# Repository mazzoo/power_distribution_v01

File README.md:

power_distribution_v01

power distribution board using XT60 connectors
and fuses with LED indicator for blown fuses

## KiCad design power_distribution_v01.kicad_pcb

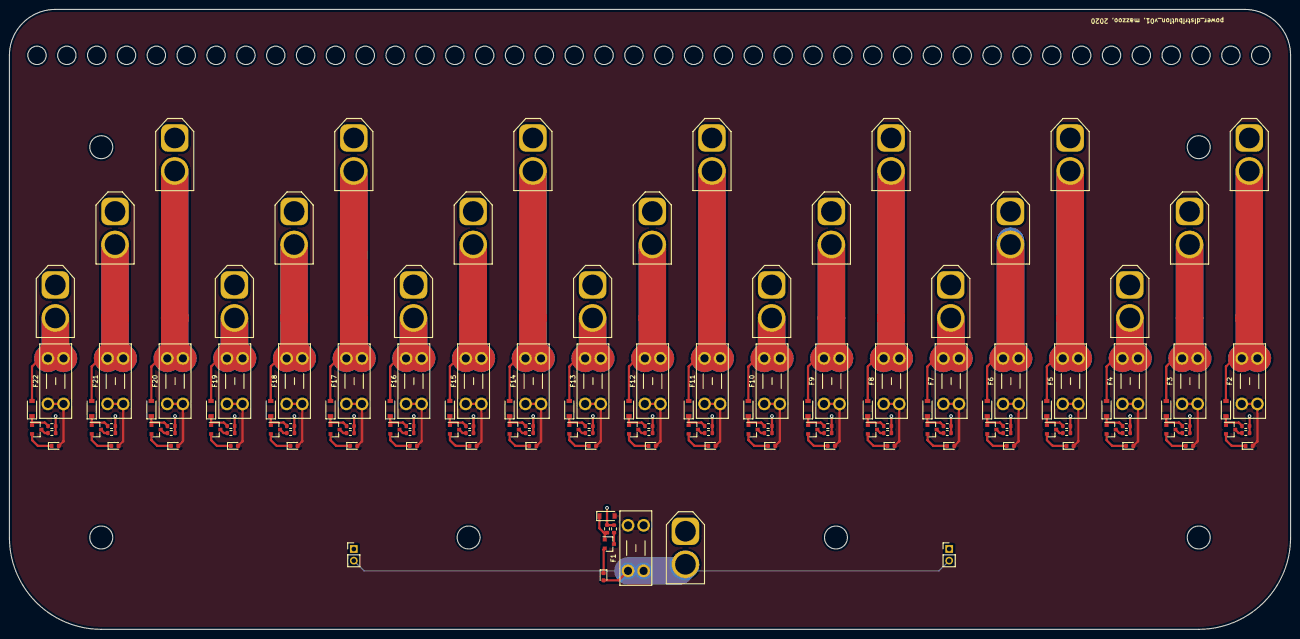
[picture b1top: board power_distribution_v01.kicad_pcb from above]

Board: 2 copper layers, 279.0 x 135.0 mm, 156 parts (0 on the bottom side), 90 nets.

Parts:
D1, D3, D5, D7, D9, D11, D13, D15, D17, D19, D21, D23, D25, D27, D29, D31, D33, D35, D37, D39, D41, D43: KT-0603R; LED_0603_1608Metric
D2, D4, D6, D8, D10, D12, D14, D16, D18, D20, D22, D24, D26, D28, D30, D32, D34, D36, D38, D40, D42, D44: 1N4148W; D_SOD-123
F1, F2, F3, F4, F5, F6, F7, F8, F9, F10, F11, F12, F13, F14, F15, F16, F17, F18, F19, F20, F21, F22: Fuse_Small; Fuseholder_Blade_Mini_Keystone_3568
J1: Conn_01x02_Male; AMASS_XT60-M_1x02_P7.20mm_Vertical
J2, J3, J4, J5, J6, J7, J8, J9, J10, J11, J12, J13, J14, J15, J16, J17, J18, J19, J20, J21, J22: Conn_01x02_Female; AMASS_XT60-F_1x02_P7.20mm_Vertical
J101, J102: Conn_01x02_Male; PinHeader_1x02_P2.54mm_Vertical
Q1, Q2, Q3, Q4, Q5, Q6, Q7, Q8, Q9, Q10, Q11, Q12, Q13, Q14, Q15, Q16, Q17, Q18, Q19, Q20, Q21, Q22: S9012; SOT-23
R1, R3, R5, R7, R9, R11, R13, R15, R17, R19, R21, R23, R25, R27, R29, R31, R33, R35, R37, R39, R41, R43: 1k; R_0603_1608Metric
R2, R4, R6, R8, R10, R12, R14, R16, R18, R20, R22, R24, R26, R28, R30, R32, R34, R36, R38, R40, R42, R44: 47k; R_0603_1608Metric

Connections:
+12V: D2.2, D3.2, D5.2, D7.2, D9.2, D11.2, D13.2, D15.2, D17.2, D19.2, D21.2, D23.2, D25.2, D27.2, D29.2, D31.2, D33.2, D35.2, D37.2, D39.2, D41.2, D43.2, F1.2, F2.1, F3.1, F4.1, F5.1, F6.1, F7.1, F8.1, F9.1, F10.1, F11.1, F12.1, F13.1, F14.1, F15.1, F16.1, F17.1, F18.1, F19.1, F20.1, F21.1, F22.1
GND: J1.1, J2.1, J3.1, J4.1, J5.1, J6.1, J7.1, J8.1, J9.1, J10.1, J11.1, J12.1, J13.1, J14.1, J15.1, J16.1, J17.1, J18.1, J19.1, J20.1, J21.1, J22.1, J101.1, J102.1, R1.2, R2.2, R3.2, R4.2, R5.2, R6.2, R7.2, R8.2, R9.2, R10.2, R11.2, R12.2, R13.2, R14.2, R15.2, R16.2, R17.2, R18.2, R19.2, R20.2, R21.2, R22.2, R23.2, R24.2, R25.2, R26.2, R27.2, R28.2, R29.2, R30.2, R31.2, R32.2, R33.2, R34.2, R35.2, R36.2, R37.2, R38.2, R39.2, R40.2, R41.2, R42.2, R43.2, R44.2
unnamed: D1.1, Q1.2
unnamed: D2.1, Q1.1, R2.1
unnamed: D3.1, Q2.2
unnamed: D4.1, Q2.1, R4.1
unnamed: D4.2, F2.2, J2.2
unnamed: D5.1, Q3.2
unnamed: D6.1, Q3.1, R6.1
unnamed: D6.2, F3.2, J3.2
unnamed: D7.1, Q4.2
unnamed: D8.1, Q4.1, R8.1
unnamed: D8.2, F4.2, J4.2
unnamed: D9.1, Q5.2
unnamed: D10.1, Q5.1, R10.1
unnamed: D10.2, F5.2, J5.2
unnamed: D11.1, Q6.2
unnamed: D12.1, Q6.1, R12.1
unnamed: D12.2, F6.2, J6.2
unnamed: D13.1, Q7.2
unnamed: D14.1, Q7.1, R14.1
unnamed: D14.2, F7.2, J7.2
unnamed: D15.1, Q8.2
unnamed: D16.1, Q8.1, R16.1
unnamed: D16.2, F8.2, J8.2
unnamed: D17.1, Q9.2
unnamed: D18.1, Q9.1, R18.1
unnamed: D18.2, F9.2, J9.2
unnamed: D19.1, Q10.2
unnamed: D20.1, Q10.1, R20.1
unnamed: D20.2, F10.2, J10.2
unnamed: D21.1, Q11.2
unnamed: D22.1, Q11.1, R22.1
unnamed: D22.2, F11.2, J11.2
unnamed: D23.1, Q12.2
unnamed: D24.1, Q12.1, R24.1
unnamed: D24.2, F12.2, J12.2
unnamed: D25.1, Q13.2
unnamed: D26.1, Q13.1, R26.1
unnamed: D26.2, F13.2, J13.2
unnamed: D27.1, Q14.2
unnamed: D28.1, Q14.1, R28.1
unnamed: D28.2, F14.2, J14.2
unnamed: D29.1, Q15.2
unnamed: D30.1, Q15.1, R30.1
unnamed: D30.2, F15.2, J15.2
unnamed: D31.1, Q16.2
unnamed: D32.1, Q16.1, R32.1
unnamed: D32.2, F16.2, J16.2
unnamed: D33.1, Q17.2
unnamed: D34.1, Q17.1, R34.1
unnamed: D34.2, F17.2, J17.2
unnamed: D35.1, Q18.2
unnamed: D36.1, Q18.1, R36.1
unnamed: D36.2, F18.2, J18.2
unnamed: D37.1, Q19.2
unnamed: D38.1, Q19.1, R38.1
unnamed: D38.2, F19.2, J19.2
unnamed: D39.1, Q20.2
unnamed: D40.1, Q20.1, R40.1
unnamed: D40.2, F20.2, J20.2
unnamed: D41.1, Q21.2
unnamed: D42.1, Q21.1, R42.1
unnamed: D42.2, F21.2, J21.2
unnamed: D43.1, Q22.2
unnamed: D44.1, Q22.1, R44.1
unnamed: D44.2, F22.2, J22.2
unnamed: Q1.3, R1.1
unnamed: Q2.3, R3.1
unnamed: Q3.3, R5.1
unnamed: Q4.3, R7.1
unnamed: Q5.3, R9.1
unnamed: Q6.3, R11.1
unnamed: Q7.3, R13.1
unnamed: Q8.3, R15.1
unnamed: Q9.3, R17.1
unnamed: Q10.3, R19.1
unnamed: Q11.3, R21.1
unnamed: Q12.3, R23.1
unnamed: Q13.3, R25.1
unnamed: Q14.3, R27.1
unnamed: Q15.3, R29.1
unnamed: Q16.3, R31.1
unnamed: Q17.3, R33.1
unnamed: Q18.3, R35.1
unnamed: Q19.3, R37.1
unnamed: Q20.3, R39.1
unnamed: Q21.3, R41.1
unnamed: Q22.3, R43.1
VCC: D1.2, F1.1, J1.2, J101.2, J102.2

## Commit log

2021-08-20 fix README
